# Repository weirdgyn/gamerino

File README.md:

# gamerino
Joypad based on Arduino Pro Micro / Leonardo board

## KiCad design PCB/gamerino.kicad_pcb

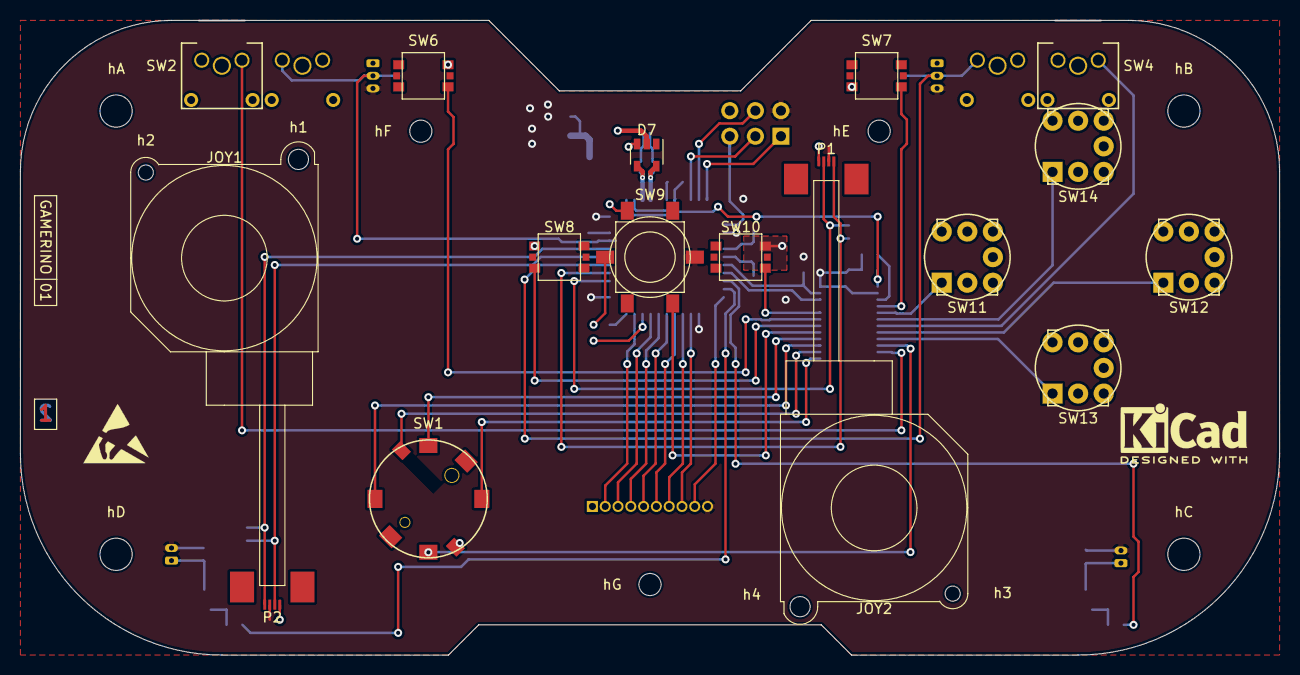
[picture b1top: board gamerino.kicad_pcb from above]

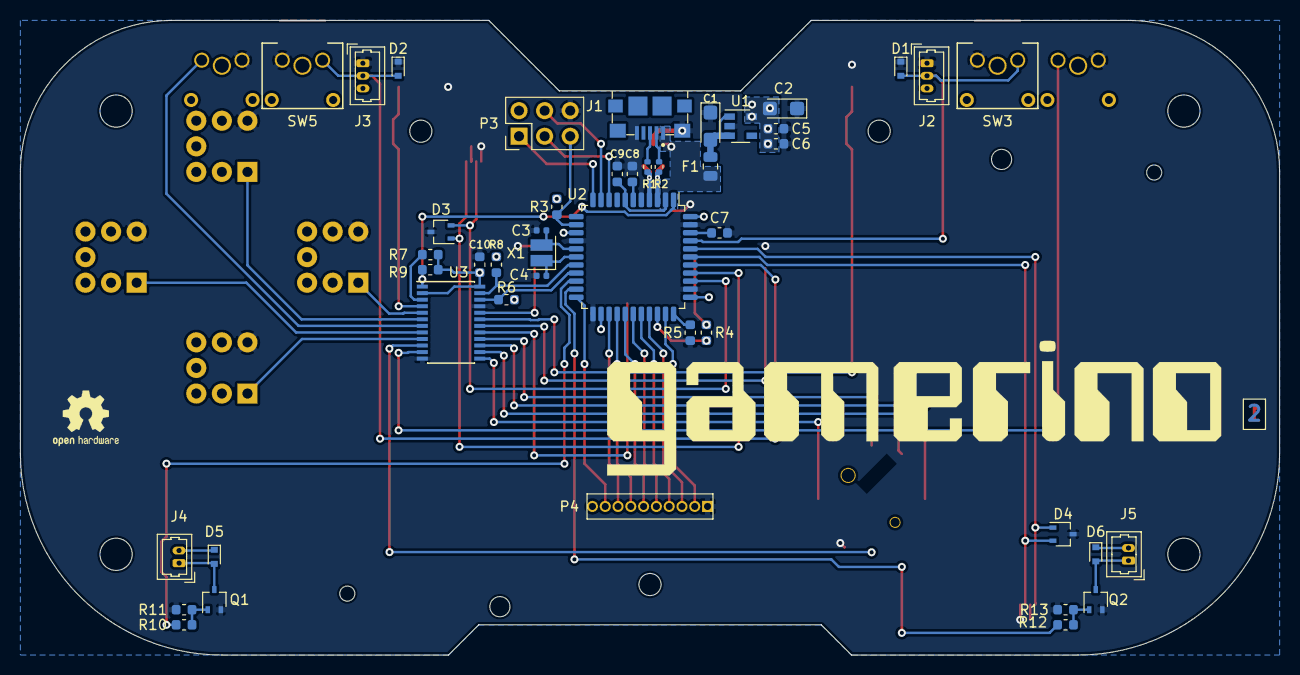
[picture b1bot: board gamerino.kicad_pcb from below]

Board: 2 copper layers, 125.0 x 63.0 mm, 77 parts (47 on the bottom side), 59 nets.

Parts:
C1, C2: 10uF; CP_EIA-3216-18_Kemet-A
C3, C4: 18pF C0G; C_0402_1005Metric
C5, C8, C9: 1uF; C_0603_1608Metric
C6, C7, C10: 100nF; C_0603_1608Metric
D1, D2: PESD5V0U1BBYL; D_SOD-523
D3, D4: D5V0L2B3W; SOT-323_SC-70
D5, D6: NSR0520V2T1G; D_SOD-523
D7: ESDS304; SOT-23-5
F1: 500mA; Fuse_0805_2012Metric
J1: USB_B_Micro; TE_1981568-1
J2: LT2; Molex_PicoBlade_53047-0310_1x03_P1.25mm_Vertical
J3: RT2; Molex_PicoBlade_53047-0310_1x03_P1.25mm_Vertical
J4, J5: ACT2; Molex_PicoBlade_53047-0210_1x02_P1.25mm_Vertical
JOY1, JOY2: RKJXU
LOGO0: LOGO-Gamerino; gamerino_logo
LOGO2: OSHW-Logo; OSHW-Logo2_7.3x6mm_SilkScreen
LOGO3: KiCad-Logo; KiCad-Logo2_5mm_SilkScreen
LOGO4: ESD-Logo; ESD-Logo_6.6x6mm_SilkScreen
P1: JOY1; 52746-0471
P2: JOY2; 52746-0471
P3: ICSP; PinHeader_2x03_P2.54mm_Vertical
P4: AUX; M52-5001045
Q1, Q2: DMN601WK; SOT-323_SC-70
R1, R2: 22R; R_0402_1005Metric
R3, R5, R7: 10K; R_0603_1608Metric
R4: 1K; R_0603_1608Metric
R6, R8, R9: 2.2K; R_0603_1608Metric
R10, R12, R13: 0R; R_0603_1608Metric
R11: 10k; R_0603_1608Metric
SW1: HATSWITCH; RKJXS
SW2: LT1; TL6215-R
SW3: LT2; TL6215-R
SW4: RT1; TL6215-R
SW5: RT2; TL6215-R
SW6: SEL; TL6210
SW7: START; TL6210
SW8: CLEAR; TL6210
SW9: TL3265
SW10: OPTS; TL6210
SW11: X; TL1220
SW12: B; TL1220
SW13: A; TL1220
SW14: Y; TL1220
U1: MIC5219-3.3YM5; SOT-23-5
U2: ATmega32U4; LQFP-44_10x10mm_P0.8mm
U3: TCA6416A; TSSOP-24_4.4x7.8mm_P0.65mm
X1: 16MHz; Crystal_SMD_2520-4Pin_2.5x2.0mm
h1, h4: 2mm; MountingHole_2mm
h2, h3: 1.5mm; MountingHole_1.5mm
hA: M3; MountingHole_3.2mm_M3
hB: M3; MountingHole_3.2mm_M3
hC: M3; MountingHole_3.2mm_M3
hD: M3; MountingHole_3.2mm_M3
hE: M2; MountingHole_2.2mm_M2
hF: M2; MountingHole_2.2mm_M2
hG: M2; MountingHole_2.2mm_M2

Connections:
+3V3: C2.2, C5.1, C6.1, C10.2, D5.1, D6.1, J2.3, J3.3, J4.2, J5.2, P1.3, P2.3, P3.2, P4.10, R3.2, R6.2, R7.2, R8.2, R9.1, SW9.6, U1.5, U2.14, U2.24, U2.34, U2.44, U3.2, U3.24
/A: SW13.1, U3.9
/B: SW12.1, U3.8
/CLEAR: SW8.2, U3.18
/HE: SW1.2, U3.13
/HN: SW1.1, U3.16
/HOME: SW9.3, U3.17
/HP: SW1.P, U3.14
/HS: SW1.3, U3.10
/HW: SW1.4, U3.15
/IRQ: R9.2, U2.1, U3.1
/J1X: D3.1, P1.4, U2.37
/J1Y: D3.2, P1.2, U2.36
/J2X: D4.1, P2.4, U2.40
/J2Y: D4.2, P2.2, U2.39
/LT1: SW2.1, U3.11
/LT2: D1.2, J2.2, SW3.1, U2.41
/MISO: P3.1, U2.11
/MOSI: P3.4, U2.10
/OPTIONS: SW10.1, U3.20
/PB4: P4.5, U2.28
/PB5: P4.4, U2.29
/PB6: P4.3, U2.30
/PC7: P4.2, U2.32
/PD2: R10.2, U2.20
/PD3: R12.2, U2.21
/PD4: P4.8, U2.25
/PD5: P4.9, U2.22
/PD6: P4.7, U2.26
/PD7: P4.6, U2.27
/RESET: P3.5, R3.1, U2.13
/RT1: SW4.1, U3.7
/RT2: D2.2, J3.2, SW5.1, U2.38
/SCK: P3.3, U2.9
/SCL: R6.1, U2.19, U3.22
/SDA: R8.1, U2.18, U3.23
/SELECT: SW6.1, U3.19
/START: SW7.1, U3.4
/X: SW11.1, U3.5
/XTAL1: C4.1, U2.17, X1.1
/XTAL2: C3.1, U2.16, X1.2
/Y: SW14.1, U3.6
ACT1-: D5.2, J4.1, Q1.3
ACT2-: D6.2, J5.1, Q2.3
D+: D7.5, R1.1, U2.4
D-: D7.4, R2.1, U2.3
GND: C1.1, C2.1, C3.2, C4.2, C5.2, C6.2, C7.1, C8.1, C9.2, C10.1, D1.1, D2.1, D3.3, D4.3, D7.2, J1.5, J1.6, J2.1, J3.1, P1.1, P2.1, P3.6, P4.1, Q1.2, Q2.2, R5.1, R11.2, R13.2, SW1.C, SW2.2, SW3.2, SW4.2, SW5.2, SW6.3, SW7.2, SW8.4, SW9.2, SW10.3, SW11.2, SW12.2, SW13.2, SW14.2, U1.2, U2.5, U2.15, U2.23, U2.35, U2.43, U3.12, U3.21
LHOME: R4.1, U2.31
unnamed: C1.2, F1.2, U1.1, U1.3
unnamed: C7.2, U2.42
unnamed: C8.2, U2.6
unnamed: J1.2, R2.2
unnamed: J1.3, R1.2
unnamed: R4.2, SW9.5
unnamed: R5.2, U2.33
unnamed: R7.1, U3.3
unnamed: Q1.1, R10.1, R11.1
unnamed: Q2.1, R12.1, R13.1
VBUS: C9.1, D7.3, F1.1, J1.1, U2.2, U2.7

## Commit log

2021-05-24 Update board
2021-05-24 Update schematics
    Add LHOME net
2021-05-25 Update Layout
2021-05-25 Update BOM
2021-05-26 Routing
2021-05-27 Layout complete
2021-05-27 Update RKJS footprint
2021-05-27 Update
    Created production files
2021-05-29 Add ESD protections to analog inputs
2021-05-29 Added datasheet
2021-05-31 Update docs, layout optimization, teardrops
2021-05-31 Optimized layout
2021-05-31 Moved pinout to docs
2024-05-21 Update LICENSE
2024-05-21 Update to KiCAD 8.0
    Update to KiCAD 8.0
